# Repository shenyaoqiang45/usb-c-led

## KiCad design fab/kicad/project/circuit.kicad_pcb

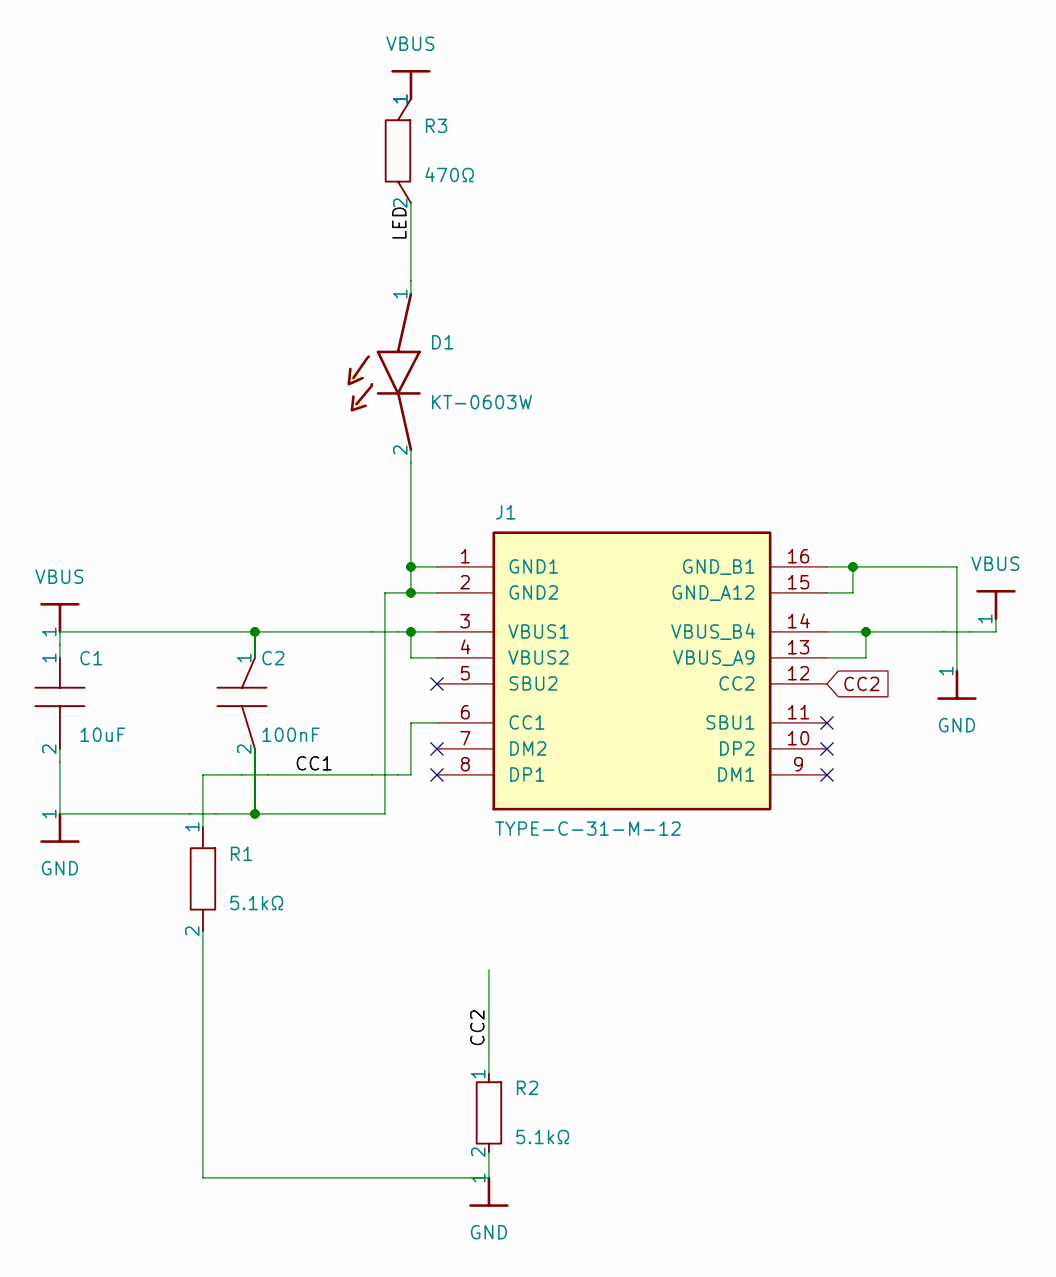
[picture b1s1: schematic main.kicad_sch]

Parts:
C1: 10uF
C2: 100nF
D1: KT-0603W
J1: TYPE-C-31-M-12
R1, R2: 5.1kΩ
R3: 470Ω

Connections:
CC1: J1.6 (CC1), R1.1
CC2: J1.12 (CC2), R2.1
GND: C1.2, C2.2, D1.2, J1.1 (GND1), J1.2 (GND2), J1.15 (GND_A12), J1.16 (GND_B1), R1.2, R2.2
LED: D1.1, R3.2
VBUS: C1.1, C2.1, J1.3 (VBUS1), J1.4 (VBUS2), J1.13 (VBUS_A9), J1.14 (VBUS_B4), R3.1

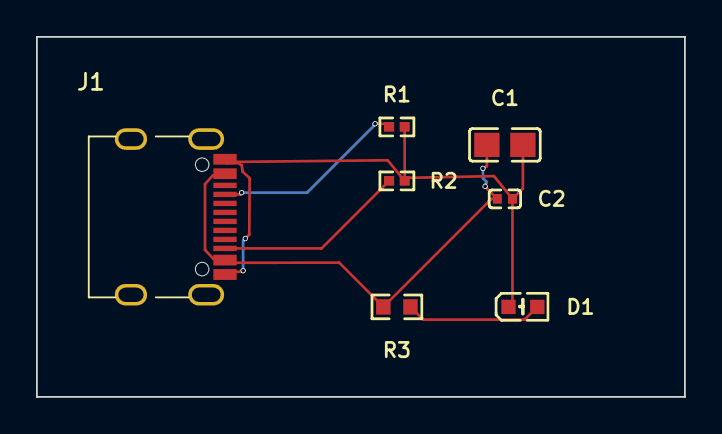
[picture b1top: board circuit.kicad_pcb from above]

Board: 2 copper layers, 36.0 x 20.0 mm, 7 parts (0 on the bottom side), 5 nets.
